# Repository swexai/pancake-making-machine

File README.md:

# System Architecture

## 1) Overview
The STM32 controller supervises three subsystems—thermal, motion, and dispense—while a hardware safety chain can de-energize heat and motion independent of firmware.

---

## 2) Power & Safety
- 230 VAC → EMI filter → MCB → RCD.  
- Branches: (a) 24 VDC controls; (b) AC heater via SSR → thermal cutoff → heater.  
- Hardware safety chain (E-STOP CH1/CH2 + cover NC) hard-cuts theta-EN & SSR.

---

## 3) Control Electronics (24 V domain)
STM32 (FreeRTOS), MAX31865 + PT100, SSR at 10 Hz, TB6600 + NEMA23 (θ), pump PWM, HMI/Logger.

---

## 4) Subsystems

### 4.1 Thermal (bake plate)
PT100 → MAX31865 → Temp PID → SSR → heater → plate. Target: 210–230 °C, ±3 °C under cycling.

### 4.2 Motion (θ-axis)
0.2 rev/s (12 RPM) with homing + jerk-limited ramps; STEP/DIR/EN → TB6600 → NEMA23; hardware EN cut.

### 4.3 Dispense (pump + manifold)
Single pump → 3-way RUN/CIP → 7-way manifold → trim/check/tube → 7 nozzles; equal-length branches; outer rings get higher mL/s.

---

## 5) Software (FreeRTOS tasks)
Safety (1 kHz), TempCtrl (25 Hz; SSR 10 Hz), ThetaCtrl (timer-driven), PumpCtrl (10 Hz), HMI (2 Hz), Logger (1 Hz).

---

## 6) Timing & Key Parameters
- θ speed: **0.2 rev/s (12 RPM)**  
- Dispense: **5 s**, **~28.3 mL/s** total (~141 mL)  
- Temp sample: **25 Hz** (PID), **10 Hz** SSR drive  
- Safety scan: **1 kHz** • Logging: **1 Hz**

---

## 7) Dispensing — 2D Drawings (SVG)
These render natively on GitHub. Place the files under `docs/architecture/svg/`.

- Top View (plate + rotating arm + 7 nozzles):  

- 2D Piping Layout (RUN/CIP + 7 branches):  

---

## 8) Video Simulation (One Revolution)
Animated visualization of a single **5 s** cycle where the arm completes **exactly one full revolution** while depositing seven concentric rings.  
Place this file at `docs/architecture/media/dispense_simulation_one_rev.gif` and embed as below:

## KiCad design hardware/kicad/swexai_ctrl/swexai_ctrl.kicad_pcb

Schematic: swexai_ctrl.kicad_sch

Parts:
H1, H2, H3, H4: MountingHole; MountingHole_3.2mm_M3

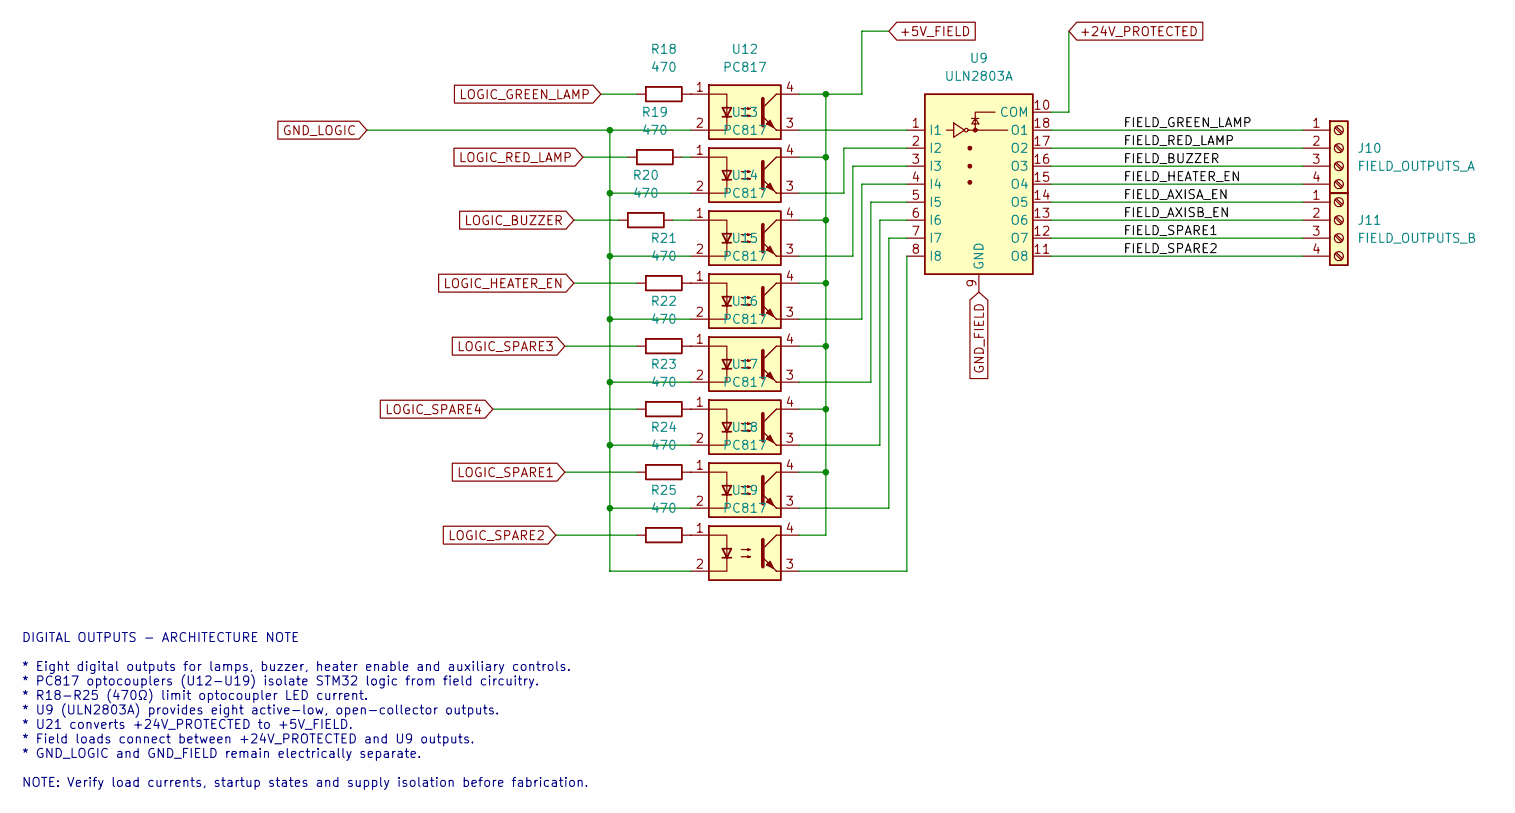
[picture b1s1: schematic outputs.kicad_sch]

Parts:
J10: FIELD_OUTPUTS_A; TerminalBlock_MaiXu_MX126-5.0-04P_1x04_P5.00mm
J11: FIELD_OUTPUTS_B; TerminalBlock_MaiXu_MX126-5.0-04P_1x04_P5.00mm
R18, R19, R20, R21, R22, R23, R24, R25: 470; R_0805_2012Metric
U9: ULN2803A; DIP-18_W7.62mm
U12, U13, U14, U15, U16, U17, U18, U19: PC817; DIP-4_W7.62mm

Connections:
+5V_FIELD: U12.4, U13.4, U14.4, U15.4, U16.4, U17.4, U18.4, U19.4; also elsewhere on the board
+24V_PROTECTED: U9.10 (COM); also elsewhere on the board
/DigitalOutputs/FIELD_AXISA_EN: J11.1, U9.14 (O5)
/DigitalOutputs/FIELD_AXISB_EN: J11.2, U9.13 (O6)
/DigitalOutputs/FIELD_BUZZER: J10.3, U9.16 (O3)
/DigitalOutputs/FIELD_GREEN_LAMP: J10.1, U9.18 (O1)
/DigitalOutputs/FIELD_HEATER_EN: J10.4, U9.15 (O4)
/DigitalOutputs/FIELD_RED_LAMP: J10.2, U9.17 (O2)
/DigitalOutputs/FIELD_SPARE1: J11.3, U9.12 (O7)
/DigitalOutputs/FIELD_SPARE2: J11.4, U9.11 (O8)
GND_FIELD: U9.9 (GND); also elsewhere on the board
GND_LOGIC: U12.2, U13.2, U14.2, U15.2, U16.2, U17.2, U18.2, U19.2; also elsewhere on the board
LOGIC_BUZZER: R20.2; also elsewhere on the board
LOGIC_GREEN_LAMP: R18.2; also elsewhere on the board
LOGIC_HEATER_EN: R21.2; also elsewhere on the board
LOGIC_RED_LAMP: R19.2; also elsewhere on the board
LOGIC_SPARE1: R24.2; also elsewhere on the board
LOGIC_SPARE2: R25.2; also elsewhere on the board
LOGIC_SPARE3: R22.2; also elsewhere on the board
LOGIC_SPARE4: R23.2; also elsewhere on the board
unnamed: R18.1, U12.1
unnamed: R19.1, U13.1
unnamed: R20.1, U14.1
unnamed: R21.1, U15.1
unnamed: R22.1, U16.1
unnamed: R23.1, U17.1
unnamed: R24.1, U18.1
unnamed: R25.1, U19.1
unnamed: U9.1 (I1), U12.3
unnamed: U9.2 (I2), U13.3
unnamed: U9.3 (I3), U14.3
unnamed: U9.4 (I4), U15.3
unnamed: U9.5 (I5), U16.3
unnamed: U9.6 (I6), U17.3
unnamed: U9.7 (I7), U18.3
unnamed: U9.8 (I8), U19.3

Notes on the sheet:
DIGITAL OUTPUTS - ARCHITECTURE NOTE * Eight digital outputs for lamps, buzzer, heater enable and auxiliary controls. * PC817 optocouplers (U12-U19) isolate STM32 logic from field circuitry. * R18-R25 (470Ω) limit optocoupler LED current. * U9 (ULN2803A) provides eight active-low, open-collector out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

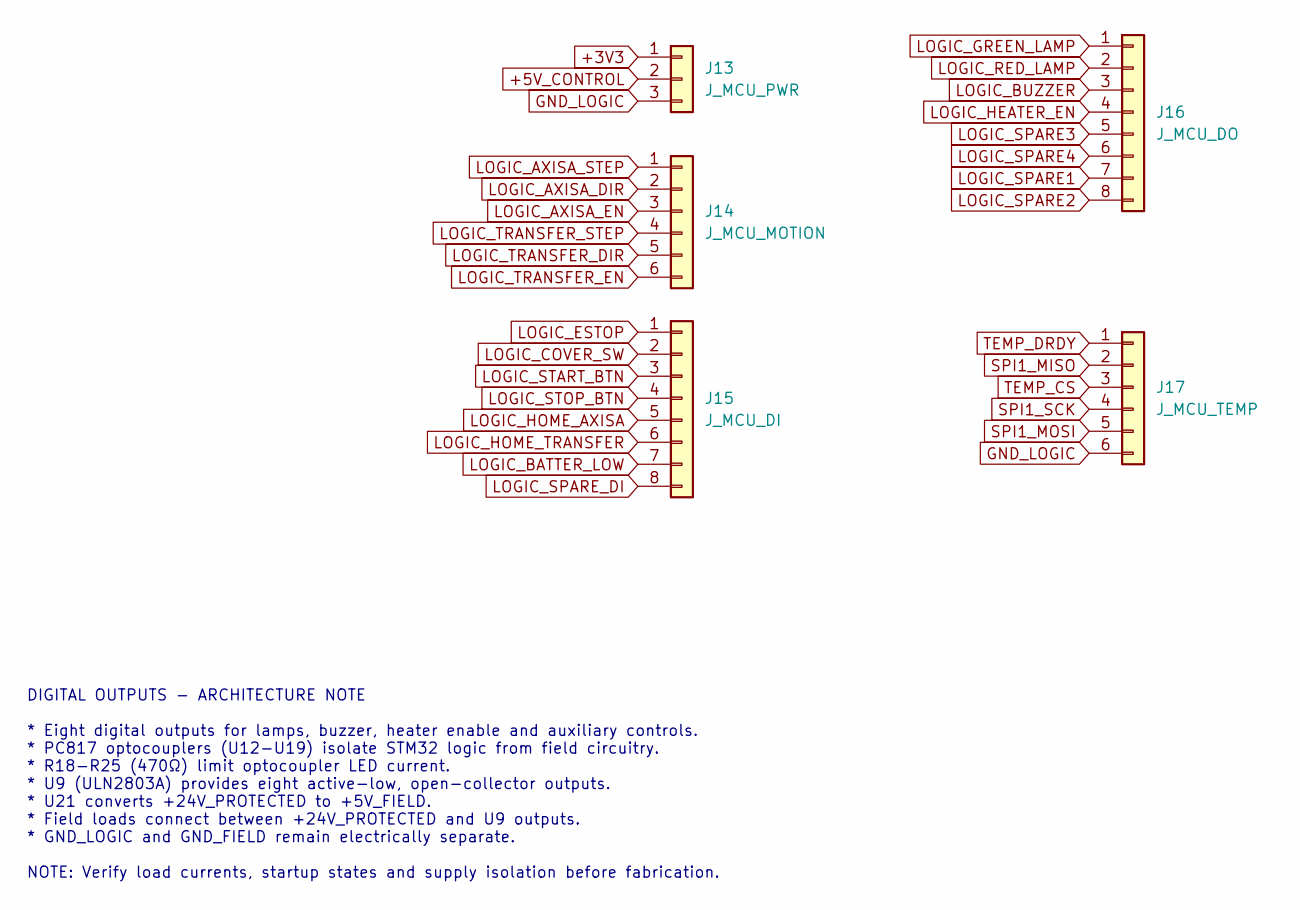
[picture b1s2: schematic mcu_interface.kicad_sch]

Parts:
J13: J_MCU_PWR; PinHeader_1x03_P2.54mm_Vertical
J14: J_MCU_MOTION; PinHeader_1x06_P2.54mm_Vertical
J15: J_MCU_DI; PinHeader_1x08_P2.54mm_Vertical
J16: J_MCU_DO; PinHeader_1x08_P2.54mm_Vertical
J17: J_MCU_TEMP; PinHeader_1x06_P2.54mm_Vertical

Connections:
+3V3: J13.1; also elsewhere on the board
+5V_CONTROL: J13.2; also elsewhere on the board
GND_LOGIC: J13.3, J17.6; also elsewhere on the board
LOGIC_AXISA_DIR: J14.2; also elsewhere on the board
LOGIC_AXISA_EN: J14.3; also elsewhere on the board
LOGIC_AXISA_STEP: J14.1; also elsewhere on the board
LOGIC_BATTER_LOW: J15.7; also elsewhere on the board
LOGIC_BUZZER: J16.3; also elsewhere on the board
LOGIC_COVER_SW: J15.2; also elsewhere on the board
LOGIC_ESTOP: J15.1; also elsewhere on the board
LOGIC_GREEN_LAMP: J16.1; also elsewhere on the board
LOGIC_HEATER_EN: J16.4; also elsewhere on the board
LOGIC_HOME_AXISA: J15.5; also elsewhere on the board
LOGIC_HOME_TRANSFER: J15.6; also elsewhere on the board
LOGIC_RED_LAMP: J16.2; also elsewhere on the board
LOGIC_SPARE1: J16.7; also elsewhere on the board
LOGIC_SPARE2: J16.8; also elsewhere on the board
LOGIC_SPARE3: J16.5; also elsewhere on the board
LOGIC_SPARE4: J16.6; also elsewhere on the board
LOGIC_SPARE_DI: J15.8; also elsewhere on the board
LOGIC_START_BTN: J15.3; also elsewhere on the board
LOGIC_STOP_BTN: J15.4; also elsewhere on the board
LOGIC_TRANSFER_DIR: J14.5; also elsewhere on the board
LOGIC_TRANSFER_EN: J14.6; also elsewhere on the board
LOGIC_TRANSFER_STEP: J14.4; also elsewhere on the board
SPI1_MISO: J17.2; also elsewhere on the board
SPI1_MOSI: J17.5; also elsewhere on the board
SPI1_SCK: J17.4; also elsewhere on the board
TEMP_CS: J17.3; also elsewhere on the board
TEMP_DRDY: J17.1; also elsewhere on the board

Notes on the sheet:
DIGITAL OUTPUTS - ARCHITECTURE NOTE * Eight digital outputs for lamps, buzzer, heater enable and auxiliary controls. * PC817 optocouplers (U12-U19) isolate STM32 logic from field circuitry. * R18-R25 (470Ω) limit optocoupler LED current. * U9 (ULN2803A) provides eight active-low, open-collector out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

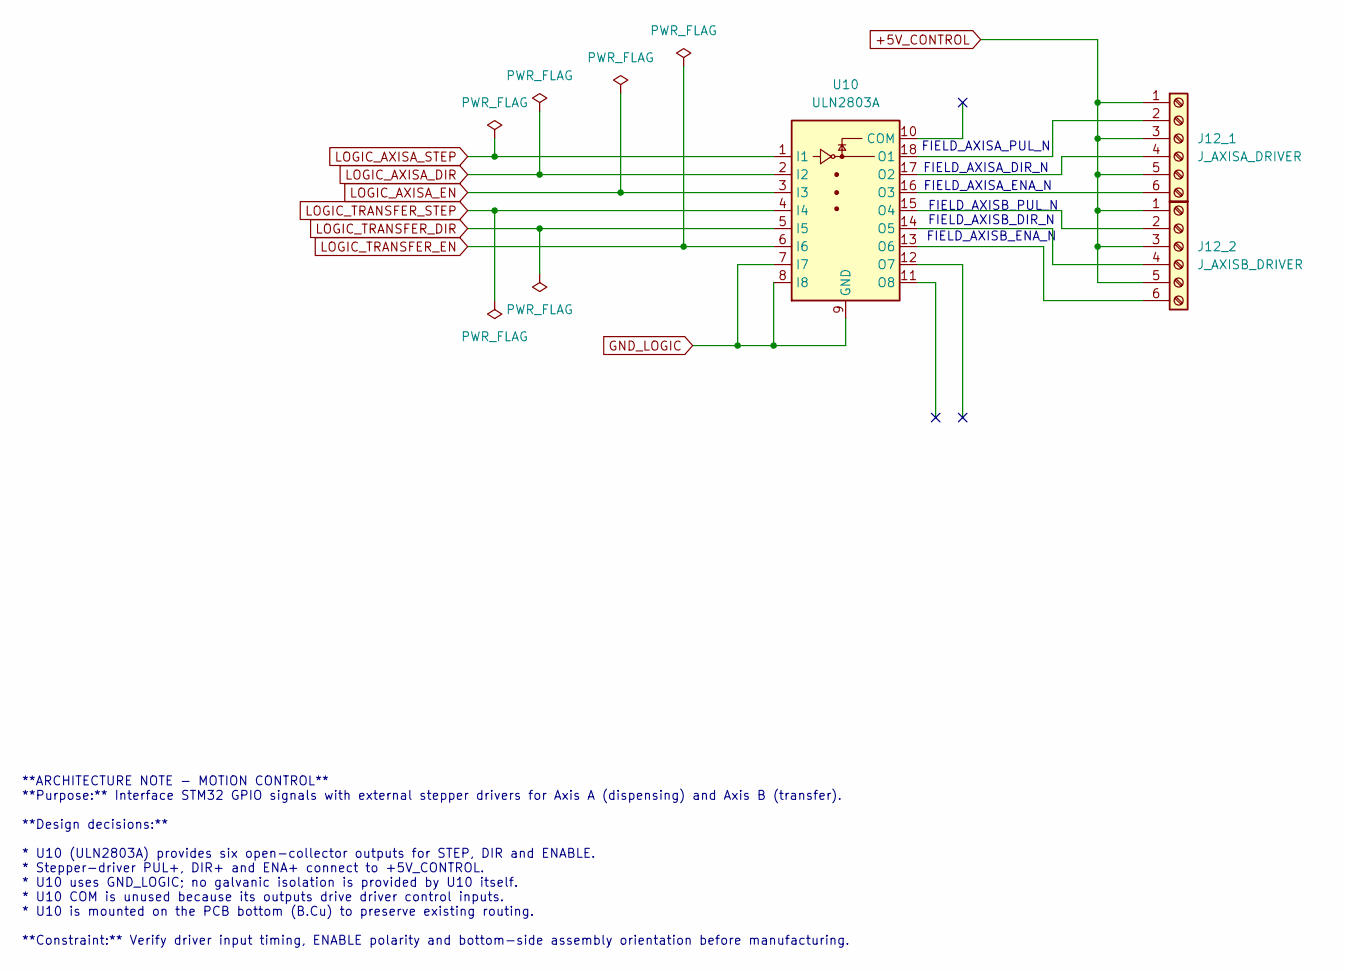
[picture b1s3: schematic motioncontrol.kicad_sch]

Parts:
J12_1: J_AXISA_DRIVER; TerminalBlock_MaiXu_MX126-5.0-06P_1x06_P5.00mm
J12_2: J_AXISB_DRIVER; TerminalBlock_MaiXu_MX126-5.0-06P_1x06_P5.00mm
U10: ULN2803A; DIP-18_W7.62mm

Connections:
+5V_CONTROL: J12_1.1, J12_1.3, J12_1.5, J12_2.1, J12_2.3, J12_2.5; also elsewhere on the board
GND_LOGIC: U10.7 (I7), U10.8 (I8), U10.9 (GND); also elsewhere on the board
LOGIC_AXISA_DIR: U10.2 (I2); also elsewhere on the board
LOGIC_AXISA_EN: U10.3 (I3); also elsewhere on the board
LOGIC_AXISA_STEP: U10.1 (I1); also elsewhere on the board
LOGIC_TRANSFER_DIR: U10.5 (I5); also elsewhere on the board
LOGIC_TRANSFER_EN: U10.6 (I6); also elsewhere on the board
LOGIC_TRANSFER_STEP: U10.4 (I4); also elsewhere on the board
unnamed: J12_1.2, U10.18 (O1)
unnamed: J12_1.4, U10.17 (O2)
unnamed: J12_1.6, U10.16 (O3)
unnamed: J12_2.2, U10.15 (O4)
unnamed: J12_2.4, U10.14 (O5)
unnamed: J12_2.6, U10.13 (O6)

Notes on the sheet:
FIELD_AXISB_DIR_N
FIELD_AXISA_ENA_N
FIELD_AXISB_PUL_N
FIELD_AXISA_PUL_N
**ARCHITECTURE NOTE - MOTION CONTROL** **Purpose:** Interface STM32 GPIO signals with external stepper drivers for Axis A (dispensing) and Axis B (transfer). **Design decisions:** * U10 (ULN2803A) provides six open-collector outputs for STEP, DIR and ENABLE. * Stepper-driver PUL+, DIR+ and ENA+ con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
FIELD_AXISB_ENA_N
FIELD_AXISA_DIR_N

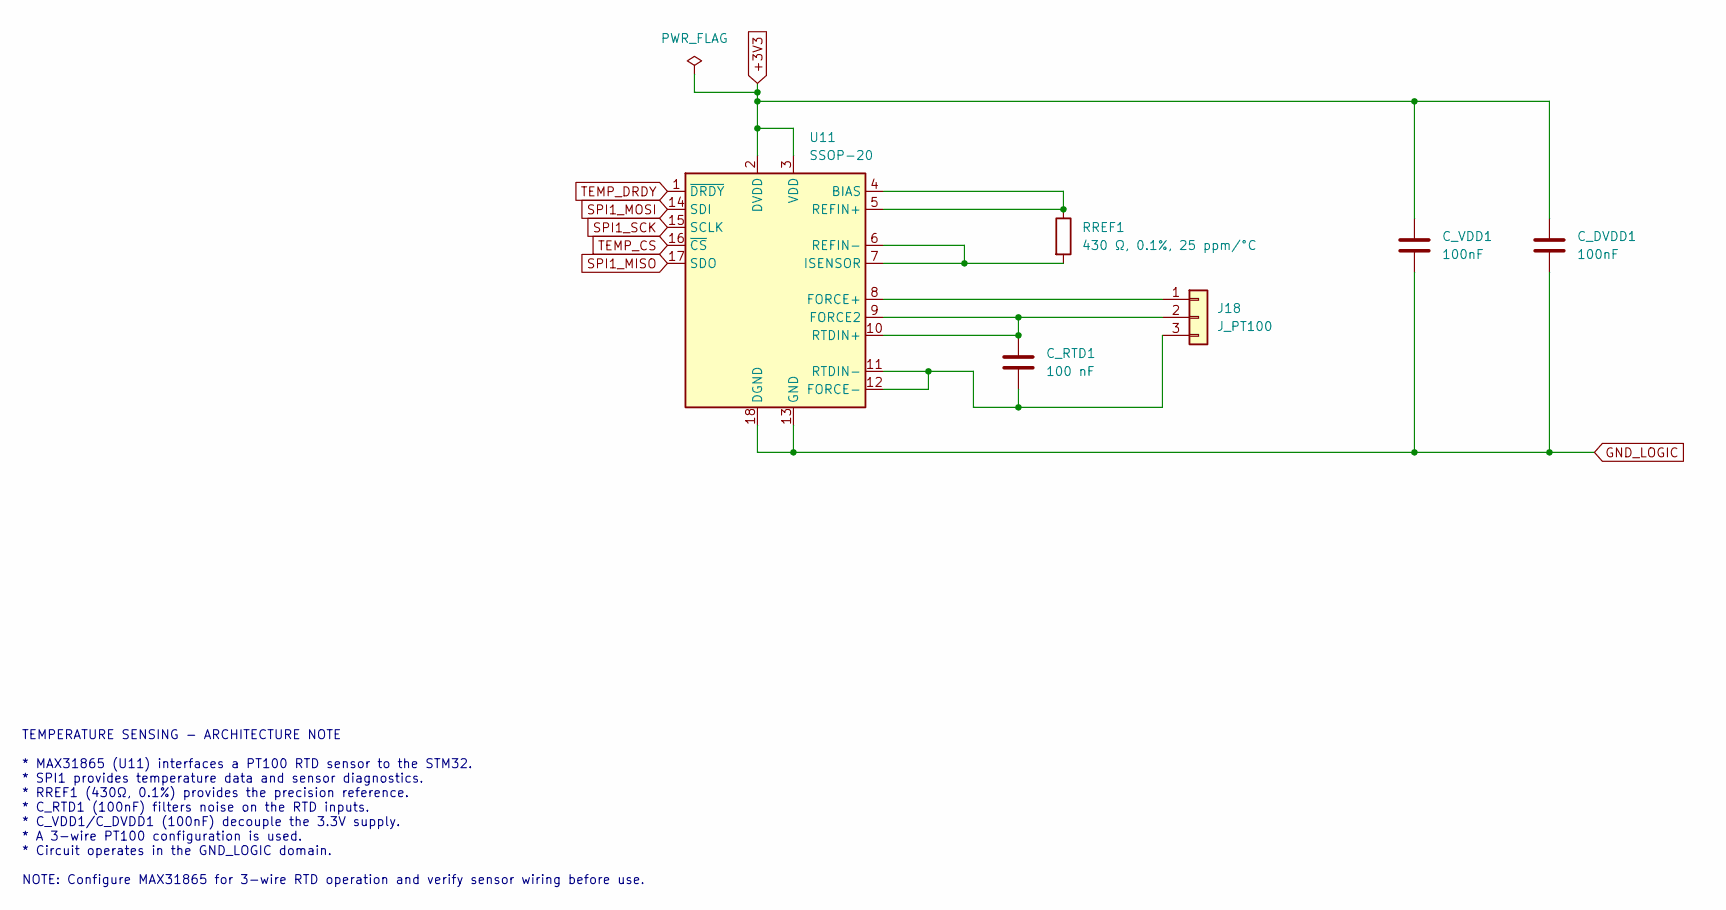
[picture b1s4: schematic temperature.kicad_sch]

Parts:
C_DVDD1: 100nF; C_0805_2012Metric
C_RTD1: 100 nF; C_0805_2012Metric
C_VDD1: 100nF; C_0805_2012Metric
J18: J_PT100; PinHeader_1x03_P2.54mm_Vertical
RREF1: 430 Ω, 0.1%, 25 ppm/°C; R_0805_2012Metric
U11: SSOP-20; SSOP-20_5.3x7.2mm_P0.65mm

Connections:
+3V3: C_DVDD1.1, C_VDD1.1, U11.2 (DVDD), U11.3 (VDD); also elsewhere on the board
GND_LOGIC: C_DVDD1.2, C_VDD1.2, U11.13 (GND), U11.18 (DGND), U11.19 (GND); also elsewhere on the board
unnamed: J18.1, U11.8 (FORCE+)
unnamed: C_RTD1.1, J18.2, U11.9 (FORCE2), U11.10 (RTDIN+)
unnamed: C_RTD1.2, J18.3, U11.11 (RTDIN-), U11.12 (FORCE-)
unnamed: RREF1.1, U11.4 (BIAS), U11.5 (REFIN+)
unnamed: RREF1.2, U11.6 (REFIN-), U11.7 (ISENSOR)
SPI1_MISO: U11.17 (SDO); also elsewhere on the board
SPI1_MOSI: U11.14 (SDI); also elsewhere on the board
SPI1_SCK: U11.15 (SCLK); also elsewhere on the board
TEMP_CS: U11.16 (~CS); also elsewhere on the board
TEMP_DRDY: U11.1 (~DRDY); also elsewhere on the board

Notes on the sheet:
TEMPERATURE SENSING - ARCHITECTURE NOTE * MAX31865 (U11) interfaces a PT100 RTD sensor to the STM32. * SPI1 provides temperature data and sensor diagnostics. * RREF1 (430Ω, 0.1%) provides the precision reference. * C_RTD1 (100nF) filters noise on the RTD inputs. * C_VDD1/C_DVDD1 (100nF) decouple th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

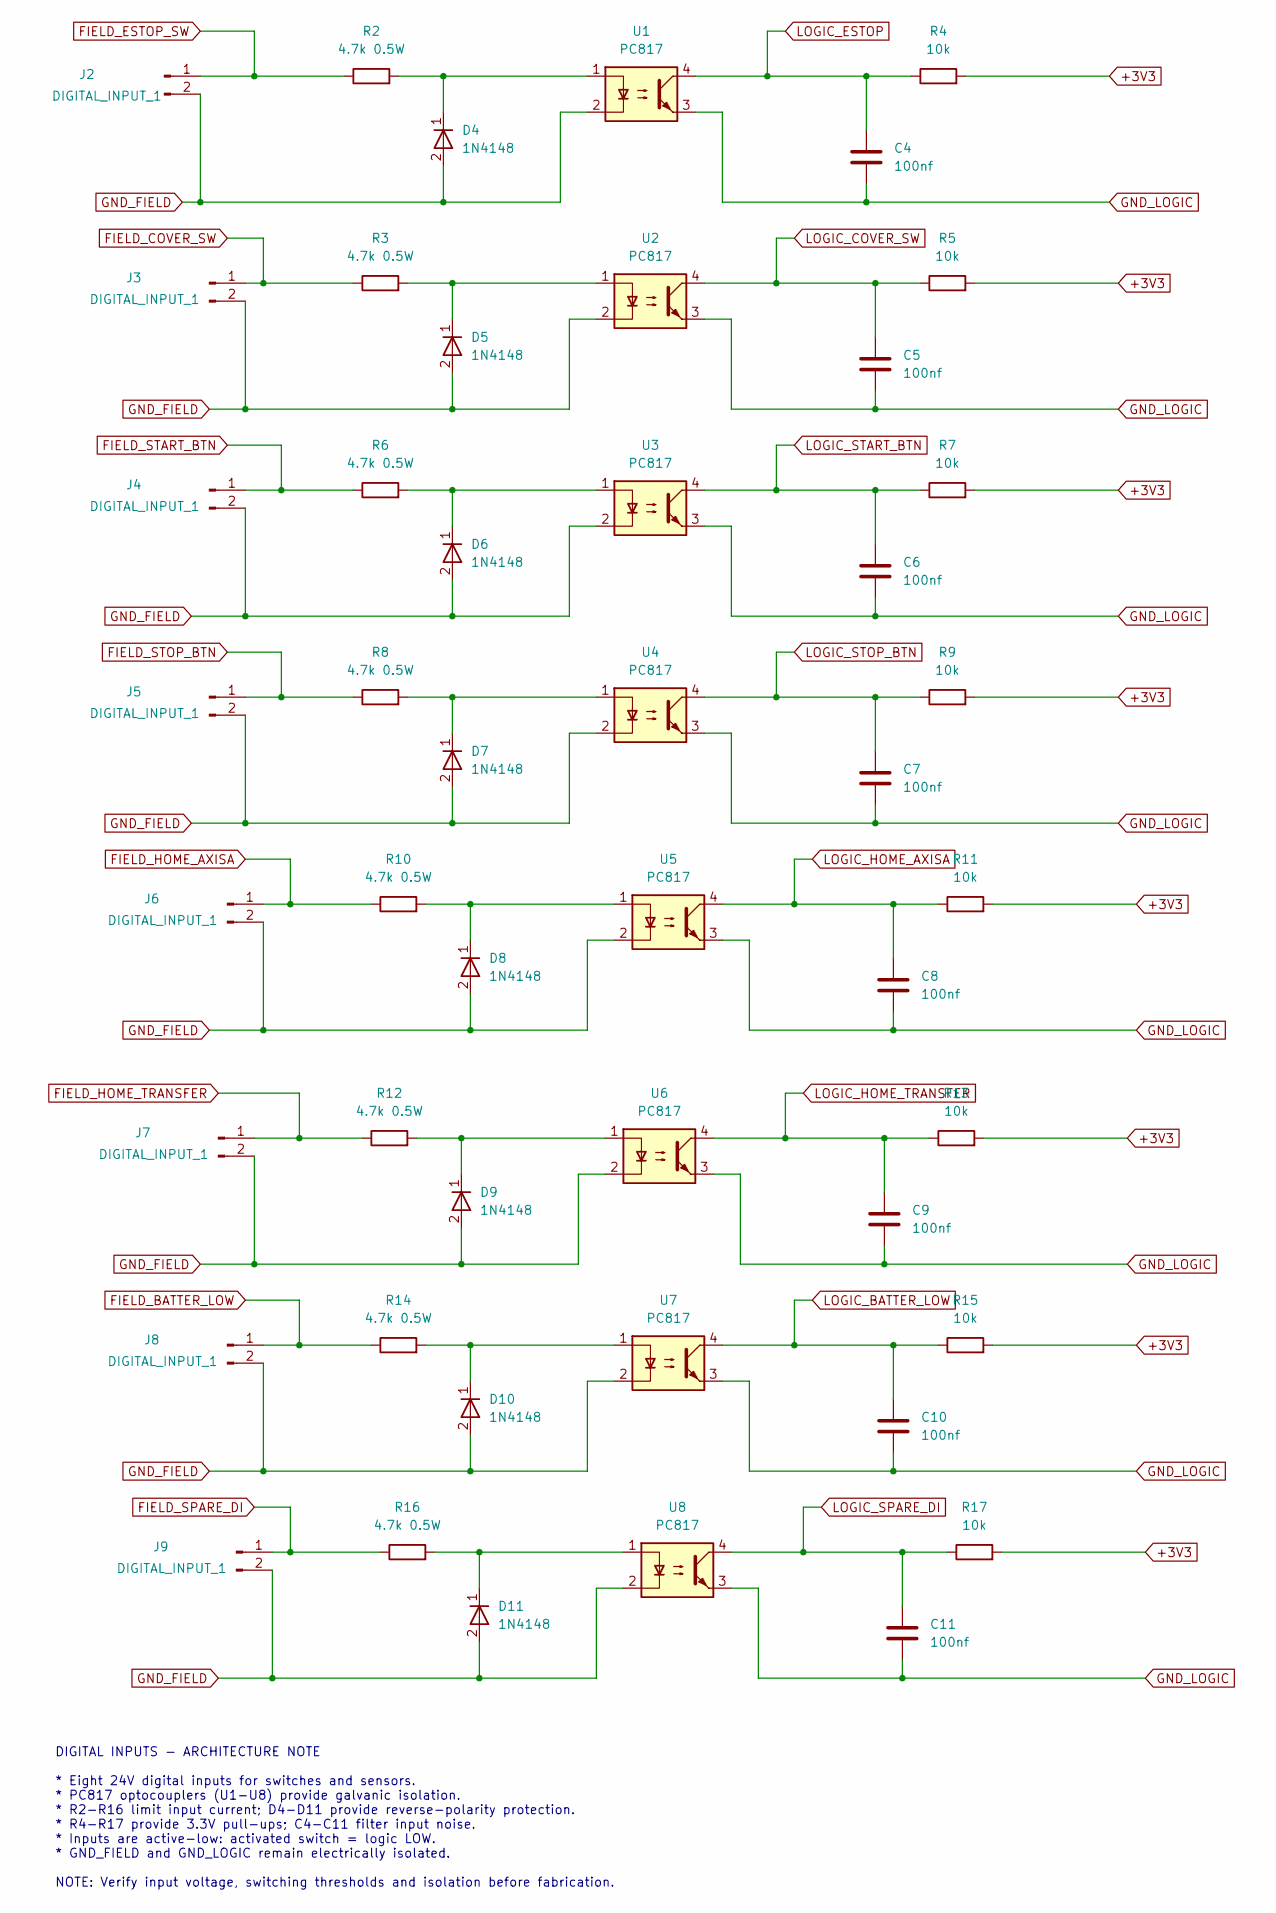
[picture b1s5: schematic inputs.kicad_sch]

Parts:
C4, C5, C6, C7, C8, C9, C10, C11: 100nf; C_0805_2012Metric
D4, D5, D6, D7, D8, D9, D10, D11: 1N4148; D_SOD-123
J2, J3, J4, J5, J6, J7, J8, J9: DIGITAL_INPUT_1; TerminalBlock_MaiXu_MX126-5.0-02P_1x02_P5.00mm
R2, R3, R6, R8, R10, R12, R14, R16: 4.7k 0.5W; R_0805_2012Metric
R4, R5, R7, R9, R11, R13, R15, R17: 10k; R_0805_2012Metric
U1, U2, U3, U4, U5, U6, U7, U8: PC817; DIP-4_W7.62mm

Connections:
+3V3: R4.2, R5.2, R7.2, R9.2, R11.2, R13.2, R15.2, R17.2; also elsewhere on the board
FIELD_BATTER_LOW: J8.1, R14.1
FIELD_COVER_SW: J3.1, R3.1
FIELD_ESTOP_SW: J2.1, R2.1
FIELD_HOME_AXISA: J6.1, R10.1
FIELD_HOME_TRANSFER: J7.1, R12.1
FIELD_SPARE_DI: J9.1, R16.1
FIELD_START_BTN: J4.1, R6.1
FIELD_STOP_BTN: J5.1, R8.1
GND_FIELD: D4.2 (A), D5.2 (A), D6.2 (A), D7.2 (A), D8.2 (A), D9.2 (A), D10.2 (A), D11.2 (A), J2.2, J3.2, J4.2, J5.2, J6.2, J7.2, J8.2, J9.2, U1.2, U2.2, U3.2, U4.2, U5.2, U6.2, U7.2, U8.2; also elsewhere on the board
GND_LOGIC: C4.2, C5.2, C6.2, C7.2, C8.2, C9.2, C10.2, C11.2, U1.3, U2.3, U3.3, U4.3, U5.3, U6.3, U7.3, U8.3; also elsewhere on the board
LOGIC_BATTER_LOW: C10.1, R15.1, U7.4; also elsewhere on the board
LOGIC_COVER_SW: C5.1, R5.1, U2.4; also elsewhere on the board
LOGIC_ESTOP: C4.1, R4.1, U1.4; also elsewhere on the board
LOGIC_HOME_AXISA: C8.1, R11.1, U5.4; also elsewhere on the board
LOGIC_HOME_TRANSFER: C9.1, R13.1, U6.4; also elsewhere on the board
LOGIC_SPARE_DI: C11.1, R17.1, U8.4; also elsewhere on the board
LOGIC_START_BTN: C6.1, R7.1, U3.4; also elsewhere on the board
LOGIC_STOP_BTN: C7.1, R9.1, U4.4; also elsewhere on the board
unnamed: D4.1 (K), R2.2, U1.1
unnamed: D5.1 (K), R3.2, U2.1
unnamed: D6.1 (K), R6.2, U3.1
unnamed: D7.1 (K), R8.2, U4.1
unnamed: D8.1 (K), R10.2, U5.1
unnamed: D9.1 (K), R12.2, U6.1
unnamed: D10.1 (K), R14.2, U7.1
unnamed: D11.1 (K), R16.2, U8.1

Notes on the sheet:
DIGITAL INPUTS - ARCHITECTURE NOTE * Eight 24V digital inputs for switches and sensors. * PC817 optocouplers (U1-U8) provide galvanic isolation. * R2-R16 limit input current; D4-D11 provide reverse-polarity protection. * R4-R17 provide 3.3V pull-ups; C4-C11 filter input noise. * Inputs are active-l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

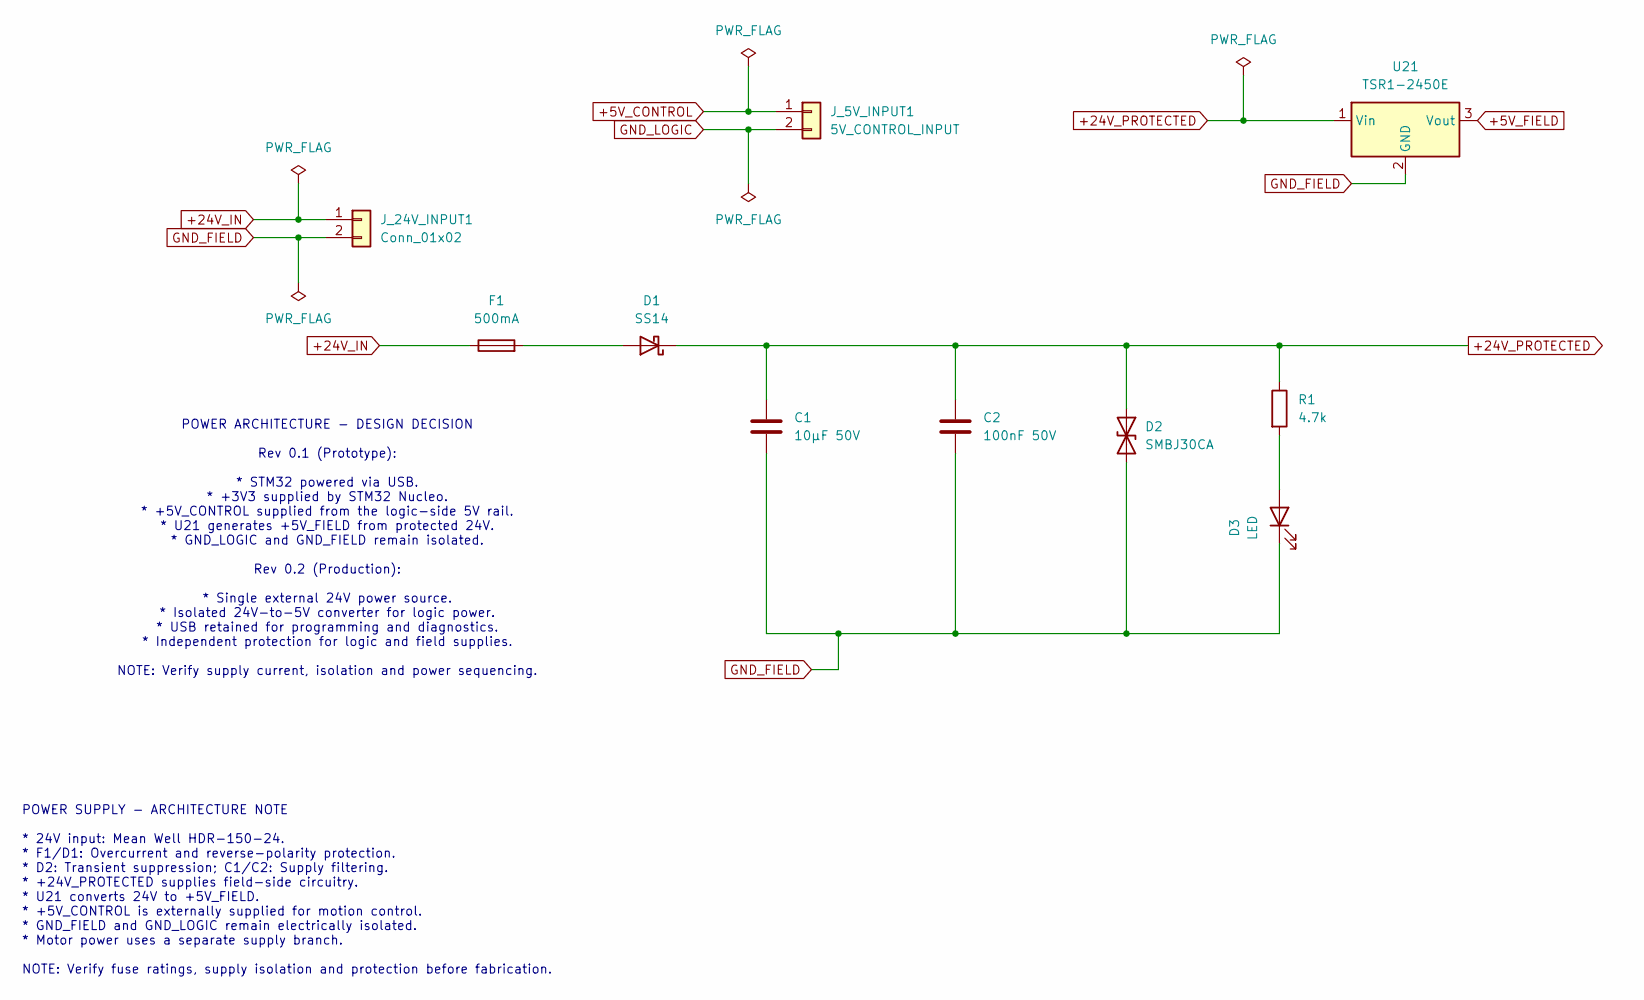
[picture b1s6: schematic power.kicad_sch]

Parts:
C1: 10µF 50V; CP_Radial_D8.0mm_P3.50mm
C2: 100nF 50V; C_0805_2012Metric
D1: SS14; D_SMA
D2: SMBJ30CA; D_SMB
D3: LED; LED_0805_2012Metric
F1: 500mA; Fuseholder_Clip-5x20mm_Bel_FC-203-22_Lateral_P17.80x5.00mm_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
J_5V_INPUT1: 5V_CONTROL_INPUT; TerminalBlock_MaiXu_MX126-5.0-02P_1x02_P5.00mm
J_24V_INPUT1: Conn_01x02; TerminalBlock_MaiXu_MX126-5.0-02P_1x02_P5.00mm
R1: 4.7k; R_0805_2012Metric
U21: TSR1-2450E; Converter_DCDC_TRACO_TSR1-xxxxE_THT

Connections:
+5V_CONTROL: J_5V_INPUT1.1; also elsewhere on the board
+5V_FIELD: U21.3 (Vout); also elsewhere on the board
+24V_IN: F1.1, J_24V_INPUT1.1
+24V_PROTECTED: C1.1, C2.1, D1.1 (K), D2.1 (A1), R1.1, U21.1 (Vin); also elsewhere on the board
GND_FIELD: C1.2, C2.2, D2.2 (A2), D3.1 (K), J_24V_INPUT1.2, U21.2 (GND); also elsewhere on the board
GND_LOGIC: J_5V_INPUT1.2; also elsewhere on the board
unnamed: D1.2 (A), F1.2
unnamed: D3.2 (A), R1.2

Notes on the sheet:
POWER ARCHITECTURE - DESIGN DECISION Rev 0.1 (Prototype): * STM32 powered via USB. * +3V3 supplied by STM32 Nucleo. * +5V_CONTROL supplied from the logic-side 5V rail. * U21 generates +5V_FIELD from protected 24V. * GND_LOGIC and GND_FIELD remain isolated. Rev 0.2 (Production): * Single external 24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
POWER SUPPLY - ARCHITECTURE NOTE * 24V input: Mean Well HDR-150-24. * F1/D1: Overcurrent and reverse-polarity protection. * D2: Transient suppression; C1/C2: Supply filtering. * +24V_PROTECTED supplies field-side circuitry. * U21 converts 24V to +5V_FIELD. * +5V_CONTROL is externally supplied for m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

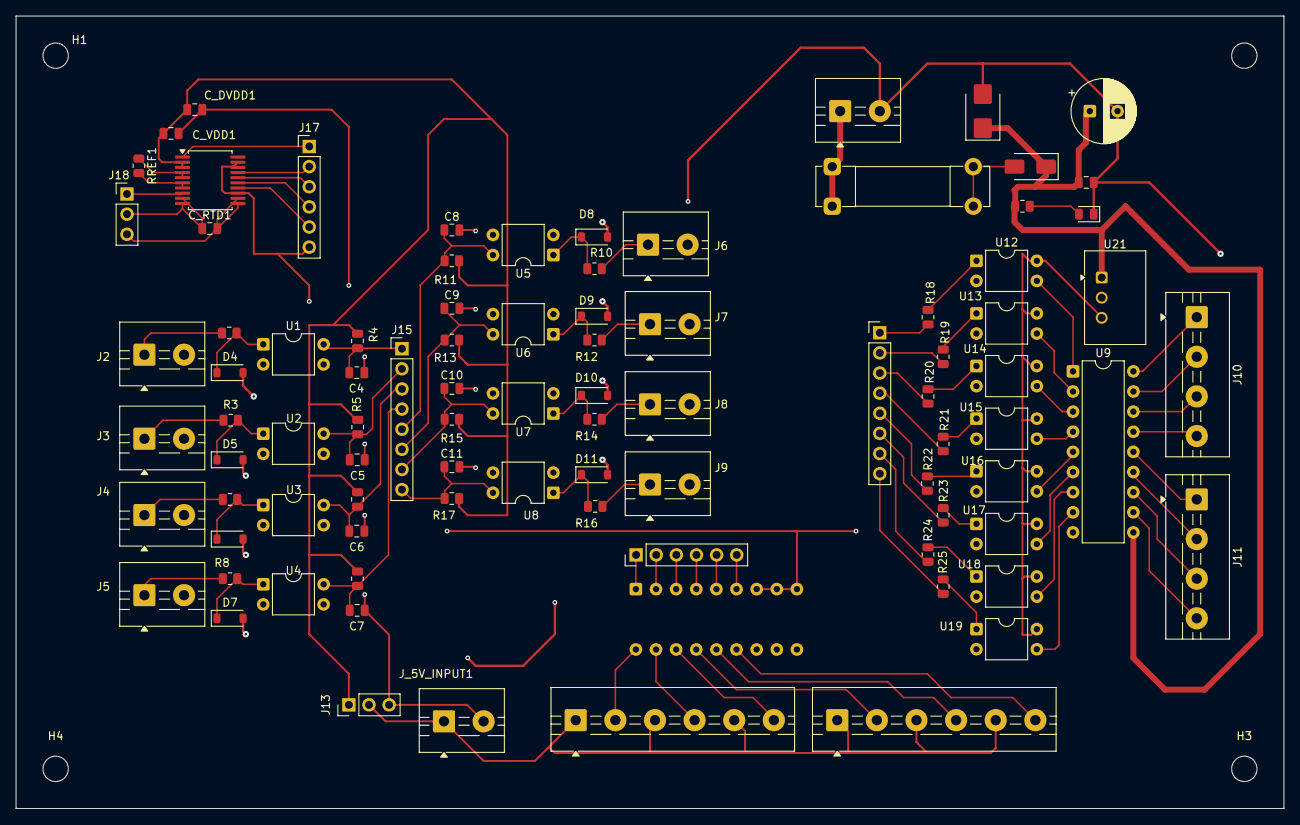
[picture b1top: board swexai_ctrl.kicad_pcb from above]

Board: 2 copper layers, 160.0 x 100.0 mm, 95 parts (1 on the bottom side), 87 nets.

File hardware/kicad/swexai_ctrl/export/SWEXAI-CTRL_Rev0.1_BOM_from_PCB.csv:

Quantity,References,Value,Footprint,Side,Manufacturer Part Number,Notes
1,C_RTD1,100 nF,Capacitor_SMD:C_0805_2012Metric,F.Cu,,PCB footprint-derived; verify purchasing part
2,"C_DVDD1, C_VDD1",100nF,Capacitor_SMD:C_0805_2012Metric,F.Cu,,PCB footprint-derived; verify purchasing part
1,C2,100nF 50V,Capacitor_SMD:C_0805_2012Metric,F.Cu,,PCB footprint-derived; verify purchasing part
8,"C4, C5, C6, C7, C8, C9, C10, C11",100nf,Capacitor_SMD:C_0805_2012Metric,F.Cu,,PCB footprint-derived; verify purchasing part
8,"R4, R5, R7, R9, R11, R13, R15, R17",10k,Resistor_SMD:R_0805_2012Metric,F.Cu,,PCB footprint-derived; verify purchasing part
1,C1,10µF 50V,Capacitor_THT:CP_Radial_D8.0mm_P3.50mm,F.Cu,,PCB footprint-derived; verify purchasing part
8,"D4, D5, D6, D7, D8, D9, D10, D11",1N4148,Diode_SMD:D_SOD-123,F.Cu,,PCB footprint-derived; verify purchasing part
1,R1,4.7k,Resistor_SMD:R_0805_2012Metric,F.Cu,,PCB footprint-derived; verify purchasing part
8,"R2, R3, R6, R8, R10, R12, R14, R16",4.7k 0.5W,Resistor_SMD:R_0805_2012Metric,F.Cu,,PCB footprint-derived; verify purchasing part
1,RREF1,"430 Ω, 0.1%, 25 ppm/°C",Resistor_SMD:R_0805_2012Metric,F.Cu,,PCB footprint-derived; verify purchasing part
8,"R18, R19, R20, R21, R22, R23, R24, R25",470,Resistor_SMD:R_0805_2012Metric,F.Cu,,PCB footprint-derived; verify purchasing part
1,F1,500mA,Fuse:Fuseholder_Clip-5x20mm_Bel_FC-203-22_Lateral_P17.80x5.00mm_D1.17mm_Horizontal,F.Cu,,PCB footprint-derived; verify purchasing part
1,J_5V_INPUT1,5V_CONTROL_INPUT,TerminalBlock:TerminalBlock_MaiXu_MX126-5.0-02P_1x02_P5.00mm,F.Cu,,PCB footprint-derived; verify purchasing part
1,J_24V_INPUT1,Conn_01x02,TerminalBlock:TerminalBlock_MaiXu_MX126-5.0-02P_1x02_P5.00mm,F.Cu,,PCB footprint-derived; verify purchasing part
8,"J2, J3, J4, J5, J6, J7, J8, J9",DIGITAL_INPUT_1,TerminalBlock:TerminalBlock_MaiXu_MX126-5.0-02P_1x02_P5.00mm,F.Cu,,PCB footprint-derived; verify purchasing part
1,J10,FIELD_OUTPUTS_A,TerminalBlock:TerminalBlock_MaiXu_MX126-5.0-04P_1x04_P5.00mm,F.Cu,,PCB footprint-derived; verify purchasing part
1,J11,FIELD_OUTPUTS_B,TerminalBlock:TerminalBlock_MaiXu_MX126-5.0-04P_1x04_P5.00mm,F.Cu,,PCB footprint-derived; verify purchasing part
1,J12_1,J_AXISA_DRIVER,TerminalBlock:TerminalBlock_MaiXu_MX126-5.0-06P_1x06_P5.00mm,F.Cu,,PCB footprint-derived; verify purchasing part
1,J12_2,J_AXISB_DRIVER,TerminalBlock:TerminalBlock_MaiXu_MX126-5.0-06P_1x06_P5.00mm,F.Cu,,PCB footprint-derived; verify purchasing part
1,J15,J_MCU_DI,Connector_PinHeader_2.54mm:PinHeader_1x08_P2.54mm_Vertical,F.Cu,,PCB footprint-derived; verify purchasing part
1,J16,J_MCU_DO,Connector_PinHeader_2.54mm:PinHeader_1x08_P2.54mm_Vertical,F.Cu,,PCB footprint-derived; verify purchasing part
1,J14,J_MCU_MOTION,Connector_PinHeader_2.54mm:PinHeader_1x06_P2.54mm_Vertical,F.Cu,,PCB footprint-derived; verify purchasing part
1,J13,J_MCU_PWR,Connector_PinHeader_2.54mm:PinHeader_1x03_P2.54mm_Vertical,F.Cu,,PCB footprint-derived; verify purchasing part
1,J17,J_MCU_TEMP,Connector_PinHeader_2.54mm:PinHeader_1x06_P2.54mm_Vertical,F.Cu,,PCB footprint-derived; verify purchasing part
1,J18,J_PT100,Connector_PinHeader_2.54mm:PinHeader_1x03_P2.54mm_Vertical,F.Cu,,PCB footprint-derived; verify purchasing part
1,D3,LED,LED_SMD:LED_0805_2012Metric,F.Cu,,PCB footprint-derived; verify purchasing part
4,"H1, H2, H3, H4",MountingHole,MountingHole:MountingHole_3.2mm_M3,F.Cu,,PCB footprint-derived; verify purchasing part
16,"U1, U2, U3, U4, U5, U6, U7, U8, U12, U13, U14, U15, U16, U17, U18, U19",PC817,Package_DIP:DIP-4_W7.62mm,F.Cu,,PCB footprint-derived; verify purchasing part
1,D2,SMBJ30CA,Diode_SMD:D_SMB,F.Cu,,PCB footprint-derived; verify purchasing part
1,D1,SS14,Diode_SMD:D_SMA,F.Cu,,PCB footprint-derived; verify purchasing part
1,U11,SSOP-20,Package_SO:SSOP-20_5.3x7.2mm_P0.65mm,F.Cu,,PCB footprint-derived; verify purchasing part
1,U21,TSR1-2450E,Converter_DCDC:Converter_DCDC_TRACO_TSR1-xxxxE_THT,F.Cu,,PCB footprint-derived; verify purchasing part
1,U10,ULN2803A,Package_DIP:DIP-18_W7.62mm,B.Cu,,PCB footprint-derived; verify purchasing part
1,U9,ULN2803A,Package_DIP:DIP-18_W7.62mm,F.Cu,,PCB footprint-derived; verify purchasing part

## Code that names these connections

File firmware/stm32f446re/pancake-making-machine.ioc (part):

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Mcu.Name=STM32F446R(C-E)Tx
Mcu.Package=LQFP64
Mcu.UserName=STM32F446RETx
PA0-WKUP.GPIOParameters=GPIO_PuPd,GPIO_Label
PA0-WKUP.GPIO_Label=ESTOP
PA0-WKUP.GPIO_PuPd=GPIO_PULLUP
PA0-WKUP.Signal=GPIO_Input
PA1.GPIOParameters=GPIO_PuPd,GPIO_Label
PA1.GPIO_Label=COVER_SW
PA1.GPIO_PuPd=GPIO_PULLUP
PA1.Signal=GPIO_Input
PA15.Signal=GPIO_Input
PA2.GPIOParameters=GPIO_Label
PA2.GPIO_Label=USART_TX
PA2.Mode=Asynchronous
PA2.Signal=USART2_TX
PA3.GPIOParameters=GPIO_Label
PA3.GPIO_Label=USART_RX
PA3.Mode=Asynchronous
PA3.Signal=USART2_RX
PA5.GPIOParameters=GPIO_Label
PA5.GPIO_Label=SPI1_CLK
PA5.Mode=Full_Duplex_Master
PA5.Signal=SPI1_SCK
PA6.Mode=Full_Duplex_Master
PA6.Signal=SPI1_MISO
PA7.Mode=Full_Duplex_Master
PA7.Signal=SPI1_MOSI
PA8.GPIOParameters=GPIO_Label
PA8.GPIO_Label=RADIAL_STEP
PA8.Signal=S_TIM1_CH1
PB3.GPIOParameters=GPIO_Label
PB3.GPIO_Label=THETA_STEP
PB3.Signal=S_TIM2_CH2
PB4.GPIOParameters=GPIO_Label
PB4.GPIO_Label=THETA_DIR
PB4.Signal=GPIO_Output
PB5.GPIOParameters=GPIO_Label
PB5.GPIO_Label=THETA_EN
PB5.Signal=GPIO_Output
PB6.GPIOParameters=GPIO_Label
PB6.GPIO_Label=PWM_PUMP
PB6.Signal=S_TIM4_CH1
PB7.GPIOParameters=GPIO_Label
PB7.GPIO_Label=Power_Indicator
PB7.Signal=GPIO_Output
PB8.GPIOParameters=GPIO_Label
PB8.GPIO_Label=RADIAL_DIR
PB8.Signal=GPIO_Output
PB9.GPIOParameters=GPIO_Label
PB9.GPIO_Label=RADIAL_EN
PB9.Signal=GPIO_Output
PC10.GPIOParameters=GPIO_Label
PC10.GPIO_Label=BATTER_LOW
PC10.Signal=GPIO_Input
PC11.GPIOParameters=GPIO_Label
PC11.GPIO_Label=SPARE_DI
PC11.Signal=GPIO_Output
PC4.GPIOParameters=GPIO_Label
PC4.GPIO_Label=START_BTN
PC4.Signal=GPIO_Output
PC5.GPIOParameters=GPIO_Label
PC5.GPIO_Label=STOP_BTN
PC5.Signal=GPIO_Output
PC6.GPIOParameters=GPIO_Label
PC6.GPIO_Label=HOME_THETA
PC6.Signal=GPIO_Output
PC7.GPIOParameters=GPIO_Label
PC7.GPIO_Label=HOME_RADIAL
PC7.Signal=GPIO_Output
board=custom

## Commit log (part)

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2026-01-10 Init project structure
2026-01-10 system overview puml
2026-01-11 git workflow
2026-01-11 Add workflow to render PlantUML diagrams to PNG
2026-01-11 Correct spelling of 'Theta' in system overview
2026-01-11 Update system overview diagram for compatibility
2026-01-11 chore(ci): render PlantUML PNGs
2026-01-11 Fix image paths in README.md
    Updated image paths in the architecture section to point to the 'docs' directory.
2026-01-11 Fix image path for Nozzle & Rings in README
2026-01-11 control design pump
2026-01-11 Fix image paths in README.md
2026-01-11 Rename control_hmi_logging.pump to control_hmi_logging.puml
2026-01-11 Rename control_overview.pump to control_overview.puml
2026-01-11 Rename control_pump_dispense.pump to control_pump_dispense.puml
2026-01-11 Rename control_theta_motion.pump to control_theta_motion.puml
2026-01-11 Rename control_safety_chain.pump to control_safety_chain.puml
2026-01-11 Rename temp_control_loop.pump to temp_control_loop.puml
2026-01-11 Update safety chain diagram for clarity and accuracy
2026-01-11 Fix UML file for temperature control loop diagram
2026-01-11 Fix image path for control overview in README
2026-01-11 Add control overview modules diagram
2026-01-11 rm pdf
2026-01-11 Refactor UML diagram connections for clarity
2026-01-11 Update HMI image filename in README
2026-01-11 Enhance system flow details in README
    Expanded the system flow section with detailed steps for power, supervision, temperature control, theta motion, dispensing, and safety chain processes.
2026-01-11 Fix formatting in system_overview.puml connections
2026-01-11 Revise README for system architecture and control design
    Updated the README to reflect new system architecture and control design sections, including detailed subsystem descriptions and diagrams.
2026-01-11 Update image reference for HMI & Logger in README
2026-01-11 Remove horizontal pump overview image from README
2026-01-11 Revise README with new images and sections
    Updated image references and added new sections for 2D drawings and video simulation.
2026-01-11 Rename control_hmi_logging.puml to control_hmi_logger.puml
2026-01-11 2d dispensing 2d piping dispensing simulation
2026-01-11 Update dispensing top view diagram
2026-01-11 Update README.md and add PDF version
2026-01-11 Remove horizontal pump overview image
    Removed horizontal pump overview image from README.
2026-01-11 Enhance PlantUML workflow for draw.io integration
    Updated the workflow to render both PlantUML and draw.io diagrams to PNG format, including changes to paths and steps for exporting and committing diagrams.
2026-01-11 Update README files and add drawio directory
2026-01-11 Refactor PlantUML workflow for clarity and updates
2026-01-11 Add fetch-depth option to checkout step
2026-03-22 ioc filed created
2026-03-22 code generated per .ioc
2026-03-22 control software added.
2026-03-22 fix: duplicate long_entry_t definition
2026-03-22 Fixes: enable uart, gpio conflicts,freertos config
2026-03-22 fix:hal_getmicrosecond,missing func declarations,missing headers
2026-03-22 fix:.cproject updated with freertos, makefile updated, subdir updated,sources.mk created
2026-03-22 fix: portENTER_CRITICAL
2026-03-28 freertos recreated in stm32ide
2026-03-28 fix:uart errors
2026-03-28 fix: motion control, uart
2026-03-28 Update: symbol + linker conflict fixed
2026-03-28 middleware files recreated after build
2026-03-28 Summary: Simulation Mode for Testing Without Hardware
2026-03-28 fix: idle task remove and stub for idle added
2026-04-07 simulation, uart working
2026-04-07 fix: transition to WARMING mode
2026-04-07 fix: enabling ssr with flag in simlation mode
2026-04-14 operator manual added
2026-05-15 motion simulation mode added
2026-05-15 motion control test
2026-06-06 PA15 removed. PB3 is step output
2026-06-13 fix: motor does not stop after entering into ESTOP
2026-06-13 fix: hmi not able to accept commands
2026-06-13 fix: hmi not reciving keyboard commands
2026-06-13 Revert regression from 3598338a: restore MODE_ESTOP and motion_disable behavior
2026-06-13 fix: hmi issue, revert to working commit
2026-06-14 fix:revert
2026-06-14 fix: syntax
2026-06-14 fix: estop not stoping the motor
2026-06-14 fix: global estop added
2026-06-15 fix: system goes to estop after homing command
